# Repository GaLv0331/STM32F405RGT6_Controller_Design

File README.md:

# ⚡️ STM32F405RGT6 Controller Design

***

## 🌟 Overview

I initially made this design for a 36V/350W motor controller but then the project was dropped, as the design is robust and flexible, it can be used in diy project or some design reference for people.

I have also included an rf module for connectivity (can be used for drones). 

Also there can be design issues in this like missing mouting holes in the pcb design(will be fixed in future revisions).

All schematics and PCB layout files were created using the **KiCad**.

***

## 🎯 Key Features and Components

| Feature | Description | Related Files |
| :--- | :--- | :--- |
| **Microcontroller** | **STM32F405RGT6** (Cortex-M4, 168 MHz) is the core processing unit. | `STM32.kicad_sch`, `STM32.kicad_pcb` |
| **Wireless Interface** | Dedicated circuitry for an **nRF** series radio module (e.g., nRF24L01). | `nrf.kicad_sch` |
| **Design Platform**| Complete PCB layout and schematic captured in KiCad. | `STM32.kicad_pro`, `STM32.kicad_pcb` |
| **Connectivity** | Includes necessary debugging headers (SWD/JTAG), power supply, and breakout points for peripherals. | |

***

## 📂 Design Files Structure

The project is managed entirely within **KiCad**. The following files are included in the main directory:

| File Name | Description |
| :--- | :--- |
| `STM32.kicad_pro` | The main KiCad project file. |
| `STM32.kicad_sch` | The primary schematic document for the STM32 controller. |
| `STM32.kicad_pcb` | The complete PCB layout file, including routing, layers, and footprints. |
| `nrf.kicad_sch` | A separate schematic sheet detailing the integration of the nRF wireless module. |
| `RF(pin change).kicad_sym` | Custom schematic symbol for the RF component or a related section. |

***

## 🛠️ Getting Started (Viewing the Design)

To open, inspect, or modify the design files, you must have KiCad installed.

### Prerequisites

1.  **KiCad EDA:** Download and install the latest stable version from the [official KiCad website](https://www.kicad.org/download/).

### How to Open

1.  **Clone the Repository:**
    ```bash
    git clone [https://github.com/GaLv0331/STM32F405RGT6_Controller_Design.git](https://github.com/GaLv0331/STM32F405RGT6_Controller_Design.git)
    ```
2.  **Open Project:** Launch KiCad and open the main project file: `STM32.kicad_pro`.
3.  From the KiCad project manager, you can then launch the Schematic Editor or the PCB Layout Editor to view the respective files.

***

## 📄 License

This project is open-source and released under the **MIT License**. See the `LICENSE` file for more details.

***

## 📞 Contact

For questions, bug reports, or contributions, please feel free to open a GitHub Issue in this repository.

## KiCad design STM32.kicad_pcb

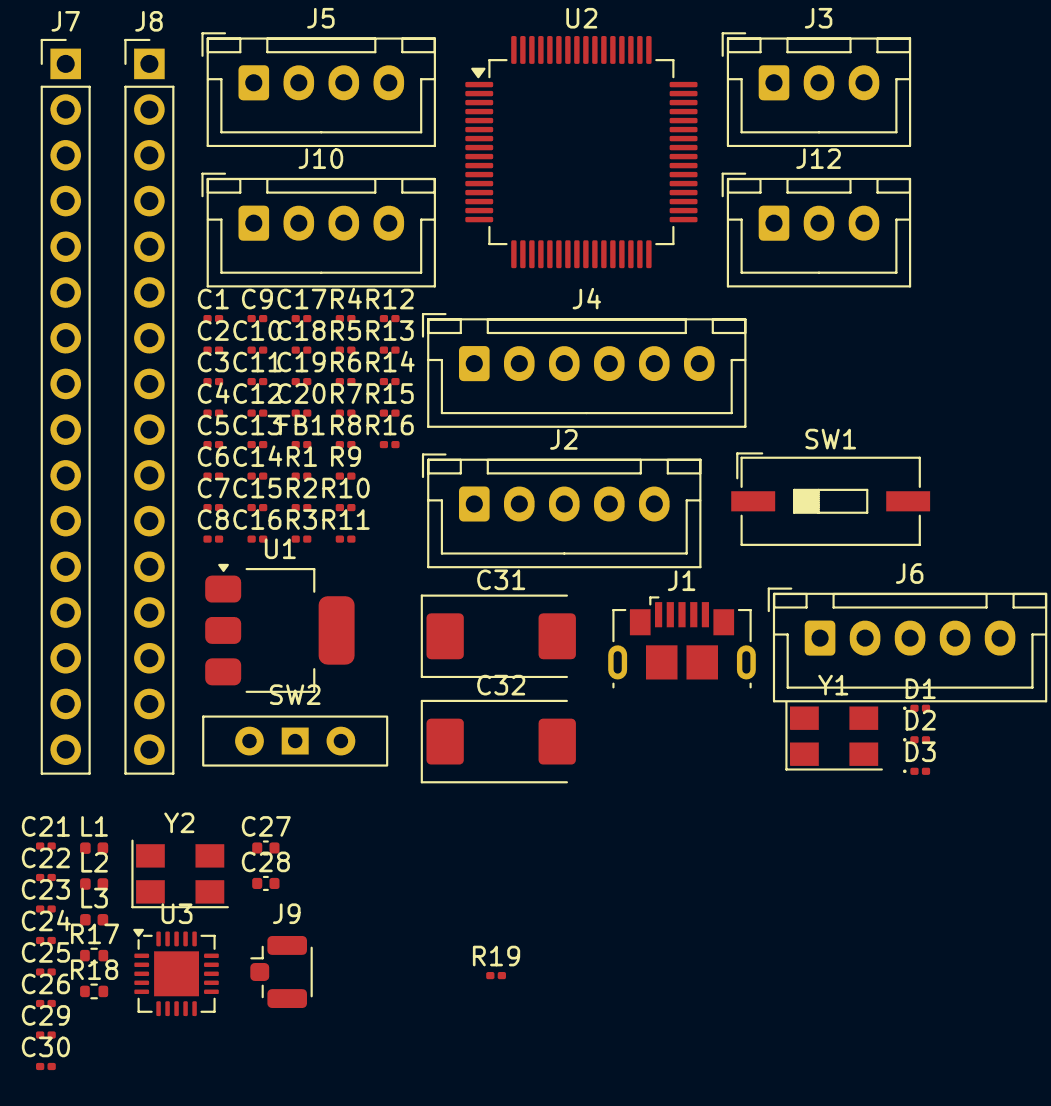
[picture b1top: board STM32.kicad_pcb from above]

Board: 2 copper layers, 76 parts (0 on the bottom side), 80 nets, no tracks yet.

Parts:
C1: 10u; C_0201_0603Metric
C2, C3, C4, C5, C6, C10, C21, C22, C23, C26: 100n; C_0201_0603Metric
C7: 10n; C_0201_0603Metric
C8, C9, C15, C16: 1u; C_0201_0603Metric
C11, C12: 2.2u; C_0201_0603Metric
C13, C14, C24, C25: 15p; C_0201_0603Metric
C17, C18, C19, C20: 4.7n; C_0201_0603Metric
C27: 1.5p; C_0402_1005Metric
C28: 1p; C_0402_1005Metric
C29: 2.2n; C_0201_0603Metric
C30: 4.7p; C_0201_0603Metric
C31, C32: 22u; CP_EIA-7343-31_Kemet-D
D1: LED_RED; LED_0201_0603Metric
D2: LED_GREEN; LED_0201_0603Metric
D3: LED_BLUE; LED_0201_0603Metric
FB1: 120R; L_0201_0603Metric
J1: USB_B_Micro; USB_Micro-B_GCT_USB3076-30-A
J2, J6: Conn_01x05; JST_XH_B5B-XH-A_1x05_P2.50mm_Vertical
J3, J12: Conn_01x03; JST_XH_B3B-XH-A_1x03_P2.50mm_Vertical
J4: Conn_01x06; JST_XH_B6B-XH-A_1x06_P2.50mm_Vertical
J5, J10: Conn_01x04; JST_XH_B4B-XH-A_1x04_P2.50mm_Vertical
J7, J8: Conn_01x16; PinHeader_1x16_P2.54mm_Vertical
J9: Conn_Coaxial; U.FL_Hirose_U.FL-R-SMT-1_Vertical
L1: 8.2n; L_0402_1005Metric
L2: 3.9n; L_0402_1005Metric
L3: 2.7n; L_0402_1005Metric
R1, R10, R11, R12, R16, R19: 10k; R_0201_0603Metric
R2, R3, R4: 0R; R_0201_0603Metric
R5, R6: 22R; R_0201_0603Metric
R7: 1k; R_0201_0603Metric
R8, R9: 220R; R_0201_0603Metric
R13, R14, R15: 2.2k; R_0201_0603Metric
R17: 22K; R_0402_1005Metric
R18: 1M; R_0402_1005Metric
SW1: SW_DIP_x01; SW_DIP_SPSTx01_Slide_9.78x4.72mm_W8.61mm_P2.54mm
SW2: SW_SPDT; SW_Slide-03_Wuerth-WS-SLTV_10x2.5x6.4_P2.54mm
U1: AMS1117-3.3; SOT-223-3_TabPin2
U2: STM32F405RGT6; LQFP-64_10x10mm_P0.5mm
U3: nRF24L01P; QFN-20-1EP_4x4mm_P0.5mm_EP2.5x2.5mm
Y1: 8Mhz 10ppm; Crystal_SMD_5032-4Pin_5.0x3.2mm
Y2: 16Mhz; Crystal_SMD_5032-4Pin_5.0x3.2mm

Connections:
+3.3V: C1.1, C2.1, C3.1, C4.1, C5.1, C6.1, C9.1, C16.1, C22.1, C23.1, C26.1, C31.1, D1.2 (A), FB1.2, J2.5, J8.15, R13.1, R14.1, R15.1, R16.2, SW2.3 (C), U1.2 (VO), U2.1 (VBAT), U2.19 (VDD), U2.32 (VDD), U2.48 (VDD), U2.64 (VDD), U3.1 (CE), U3.7 (VDD), U3.15 (VDD), U3.17 (VSS)
+3.3VA: C7.1, C8.1, FB1.1, U2.13 (VDDA)
+5V: C15.1, C32.1, J3.3, J4.6, J5.4, J6.5, J8.16, J12.3, R4.1, U1.3 (VI)
/ADC_15: J3.2, U2.25 (PC5)
/Battery_Level: J7.8, U2.11 (PC3)
/BrakeL_EXTI2: J10.4, U2.55 (PB3)
/BrakeR_EXTI3: J10.2, U2.56 (PB4)
/Current_Phase_A: J7.5, U2.8 (PC0)
/Current_Phase_B: J7.6, U2.9 (PC1)
/Current_Phase_C: J7.7, U2.10 (PC2)
/EN_GATE: J8.13, U2.57 (PB5)
/FAULT: J8.14, U2.59 (PB7)
/HALL_A: C18.1, R10.2, U2.37 (PC6)
/HALL_B: C19.1, R11.2, U2.38 (PC7)
/HALL_C: C20.1, R12.2, U2.39 (PC8)
/LED_BLUE: D3.2 (A), U2.27 (PB1)
/LED_GREEN: D2.2 (A), U2.26 (PB0)
/Mosfet_temp: J7.12, U2.17 (PA3)
/Motor Temp: C17.1, J4.5, R16.1, U2.24 (PC4)
/PAS_EXTI1: J12.2, R19.2, U2.58 (PB6)
/PB2: J7.13, U2.28 (PB2)
/PC9: J8.4, U2.40 (PC9)
/PC13: J7.3, U2.2 (PC13)
/PC14: J7.2, U2.3 (PC14)
/PC15: J7.1, U2.4 (PC15)
/PD2: J8.12, U2.54 (PD2)
/S810_CLK: J6.2, U2.33 (PB12)
/S810_RX: J6.3, U2.30 (PB11)
/S810_TX: J6.4, U2.29 (PB10)
/SCL: J5.3, U2.61 (PB8)
/SDA: J5.2, U2.62 (PB9)
/SPI3_CS: J8.8, U2.50 (PA15)
/SPI3_MISO: J8.10, U2.52 (PC11)
/SPI3_MOSI: J8.11, U2.53 (PC12)
/SPI3_SCLK: J8.9, U2.51 (PC10)
/SWCLK: J2.4, U2.49 (PA14)
/SWDIO: J2.2, U2.46 (PA13)
/SW_Boot0: R1.1, SW2.2 (B)
/USB_DM: R5.1, U2.44 (PA11)
/USB_DP: R6.1, U2.45 (PA12)
/Voltage_1: J7.9, U2.14 (PA0)
/Voltage_2: J7.10, U2.15 (PA1)
/Voltage_3: J7.11, U2.16 (PA2)
/input_HA: J8.5, U2.41 (PA8)
/input_HB: J8.6, U2.42 (PA9)
/input_HC: J8.7, U2.43 (PA10)
/input_LA: J8.1, U2.34 (PB13)
/input_LB: J8.2, U2.35 (PB14)
/input_LC: J8.3, U2.36 (PB15)
/nRST: C10.1, J2.1, J7.4, SW1.2, U2.7 (NRST)
/nrf_CSN: U2.20 (PA4), U3.2 (CSN)
/nrf_MISO: U2.22 (PA6), U3.5 (MISO)
/nrf_MOSI: U2.23 (PA7), U3.4 (MOSI)
/nrf_SCK: U2.21 (PA5), U3.3 (SCK)
GND: C1.2, C2.2, C3.2, C4.2, C5.2, C6.2, C7.2, C8.2, C9.2, C10.2, C11.2, C12.2, C13.2, C14.2, C15.2, C16.2, C17.2, C18.2, C19.2, C20.2, C21.1, C22.2, C23.2, C24.2, C25.2, C26.2, C28.2, C29.2, C30.2, C31.2, C32.2, J1.5 (GND), J1.6 (Shield), J2.3, J3.1, J4.1, J5.1, J6.1, J7.15, J7.16, J9.2 (Ext), J10.1, J10.3, J12.1, R7.1, R8.1, R9.1, R17.1, R19.1, SW1.1, SW2.1 (A), U1.1 (GND), U2.12 (VSSA), U2.18 (VSS), U2.63 (VSS), U3.8 (VSS), U3.14 (VSS), U3.18 (VDD), U3.20 (VSS), U3.21 (GND_PAD), Y1.2, Y1.4, Y2.2, Y2.4
unnamed: C13.1, R3.1, Y1.3
unnamed: C14.1, R2.1, Y1.1
unnamed: C27.1, L2.1
unnamed: D1.1 (K), R7.2
unnamed: D2.1 (K), R8.2
unnamed: D3.1 (K), R9.2
unnamed: J1.3 (D+), R6.2
unnamed: J1.2 (D-), R5.2
unnamed: J1.1 (VBUS), R4.2
unnamed: J4.2, R12.1, R15.2
unnamed: J4.3, R11.1, R14.2
unnamed: J4.4, R10.1, R13.2
unnamed: C27.2, C28.1, J9.1 (In)
unnamed: R1.2, U2.60 (BOOT0)
unnamed: R3.2, U2.5 (PH0)
unnamed: R2.2, U2.6 (PH1)
unnamed: C12.1, U2.31 (VCAP_1)
unnamed: C11.1, U2.47 (VCAP_2)
unnamed: L1.2, L3.2, U3.12 (ANT1)
unnamed: L1.1, L2.2, U3.13 (ANT2)
unnamed: C21.2, U3.19 (DVDD)
unnamed: R17.2, U3.16 (IREF)
unnamed: C29.1, C30.1, L3.1, U3.11 (VDD_PA)
unnamed: C25.1, R18.1, U3.10 (XC1), Y2.1
unnamed: C24.1, R18.2, U3.9 (XC2), Y2.3

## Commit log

2025-12-02 Rename layout.jpeg to assets/layout.jpeg
2025-12-02 Rename pcb_design.png to assests/pcb_design.png
2025-12-02 Rename pcb_design.png to pcb_design.png
2025-12-02 Rename stm32f405rgt6.pdf to stm32f405rgt6.pdf
